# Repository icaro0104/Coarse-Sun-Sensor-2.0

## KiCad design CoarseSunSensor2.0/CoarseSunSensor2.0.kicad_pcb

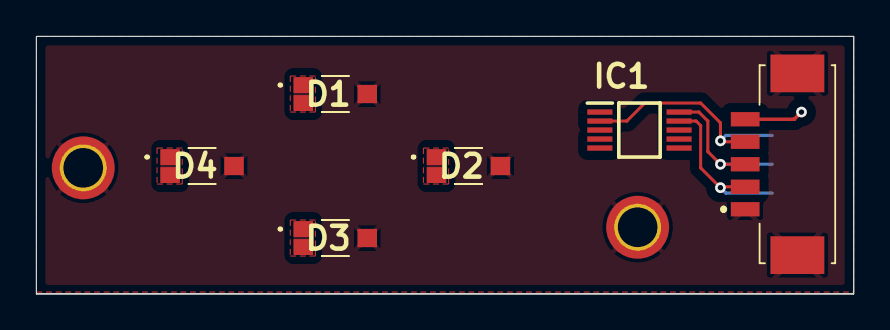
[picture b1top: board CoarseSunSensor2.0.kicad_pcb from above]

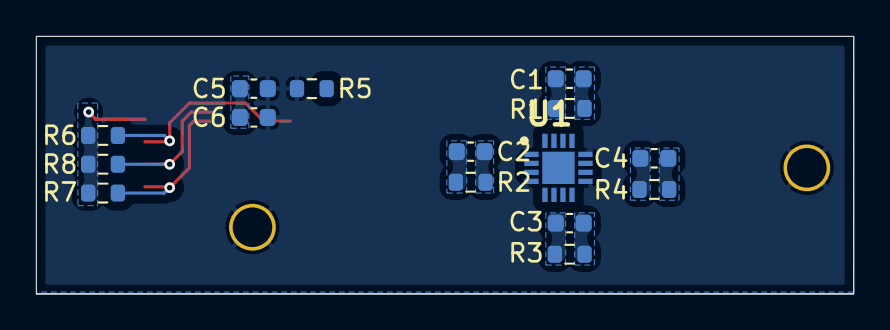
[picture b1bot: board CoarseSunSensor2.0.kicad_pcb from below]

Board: 2 copper layers, 45.4 x 14.3 mm, 23 parts (15 on the bottom side), 14 nets.

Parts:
C1, C2, C3, C4: C; C_0603_1608Metric
C5: 4.7u; C_0603_1608Metric
C6: 100n; C_0603_1608Metric
D1, D2, D3, D4: VEMD6060X01
H1, H2: MountingHole_Pad; MountingHole_2.2mm_M2_ISO7380_Pad_TopOnly
IC1: ADS1115IDGSR; SOP50P490X110-10N
J1: 53261-0571; 532610571TR250
R1, R2, R3, R4: R; R_0603_1608Metric
R5, R6, R7, R8: 10K; R_0603_1608Metric
U1: QFN50P300X300X100-17N

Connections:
+3V3: C5.2, C6.2, IC1.8 (VDD), J1.5, R6.2, R7.2, R8.2, U1.2
/16bit I2C ADC/IN0: C1.2, IC1.4 (AIN0), R1.2, U1.15
/16bit I2C ADC/IN1: C2.2, IC1.5 (AIN1), R2.2, U1.6
/16bit I2C ADC/IN2: C3.2, IC1.6 (AIN2), R3.2, U1.7
/16bit I2C ADC/IN3: C4.2, IC1.7 (AIN3), R4.2, U1.14
/16bit I2C ADC/SDA: IC1.9 (SDA), J1.2, R7.1
/16bit I2C ADC/SLC: IC1.10 (SCL), J1.3, R8.1
/16bit I2C ADC/alert/ready: IC1.2 (ALERT/RDY), J1.4, R6.1
GND: C5.1, C6.1, D1.3 (CATHODE), D2.3 (CATHODE), D3.3 (CATHODE), D4.3 (CATHODE), H1.1, H2.1, IC1.3 (GND), J1.1, J1.MP1, J1.MP2, R5.1, U1.1 (+), U1.4 (+), U1.9 (+), U1.11, U1.12 (+)
unnamed: C1.1, D1.1 (ANODE_1), D1.2 (ANODE_2), R1.1, U1.16 (-)
unnamed: C2.1, D2.1 (ANODE_1), D2.2 (ANODE_2), R2.1, U1.5 (-)
unnamed: C3.1, D3.1 (ANODE_1), D3.2 (ANODE_2), R3.1, U1.8 (-)
unnamed: C4.1, D4.1 (ANODE_1), D4.2 (ANODE_2), R4.1, U1.13 (-)
unnamed: IC1.1 (ADDR), R5.2

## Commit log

2025-06-06 buuuunch of stuff
2025-06-07 Layout done
